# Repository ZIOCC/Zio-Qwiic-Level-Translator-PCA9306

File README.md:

# Zio Qwiic Level Translator (PCA9306)

> This product can be available for purchase [here](https://www.smart-prototyping.com/Zio-Qwiic-Level-Translator-PCA9306).

#### Description

Does your project use components with different voltages? There must be a way to match the output level of one device with the input voltage level of another device.To allow a proper translation of I2C signals from one voltage reference to another, both the high-level and low-level voltage thresholds need to be translated. No worries, we got you covered with the ZIO Qwiic Level Translator allowing bidirectional voltage translation from 1V to 3.6V and 1.8V to 5.5V on the high side.  

The board features a PCA9306 Dual bidirectional I2C bus and SMBUS voltage level translator without the use of a direction pin. Not only capable to match voltages but also frequencies, so it can be used to run two buses at different frequencies. One at 400 kHz operating frequency, and the other at 100 kHz.

As part of our Qwiic family, the setup is basic, just connect the lower voltage part to the connector next to SCL1, SDA1 and AREF1. The higher voltage part is connected the opposite connector next to SCL2, SDA2 and ARED2. 

We’ve also included the pinout in case you want to have the access directly to the connections. 

#### Specification

* Interface: I2C
* Allows voltage level translation between:
  * 1.0 V Vref(1) and 1.8 V, 2.5 V, 3.3 V or 5 V Vbias(ref)(2)
  * 1.2 V Vref(1) and 1.8 V, 2.5 V, 3.3 V or 5 V Vbias(ref)(2)
  * 1.8 V Vref(1) and 3.3 V or 5 V Vbias(ref)(2)
  * 2.5 V Vref(1) and 5 V Vbias(ref)(2)
  * 3.3 V Vref(1) and 5 V Vbias(ref)(2)
* Provides bidirectional voltage translation with no direction pin
* Less than 1.5 ns maximum propagation delay to accommodate Standard-mode and Fast-mode I2C-bus devices and multiple masters
* Low 3.5  ON-state connection between input and output ports provides less signal distortion
* Dimensions: 18.4 x 19.9mm
* Weight: 1.2g

#### Links

* [Eagle File and Schematic](https://github.com/ZIOCC/Zio-Qwiic-Level-Translator-PCA9306)
* [PCA9306 Datasheet](http://www.ti.com/lit/ds/symlink/pca9306.pdf)

> ###### About Zio
> Zio is a new line of open sourced, compact, and grid layout boards, fully integrated for Arduino and Qwiic ecosystem. Designed ideally for wearables, robotics, small-space limitations or other on the go projects. Check out other awesome Zio products [here](https://www.smart-prototyping.com/Zio).

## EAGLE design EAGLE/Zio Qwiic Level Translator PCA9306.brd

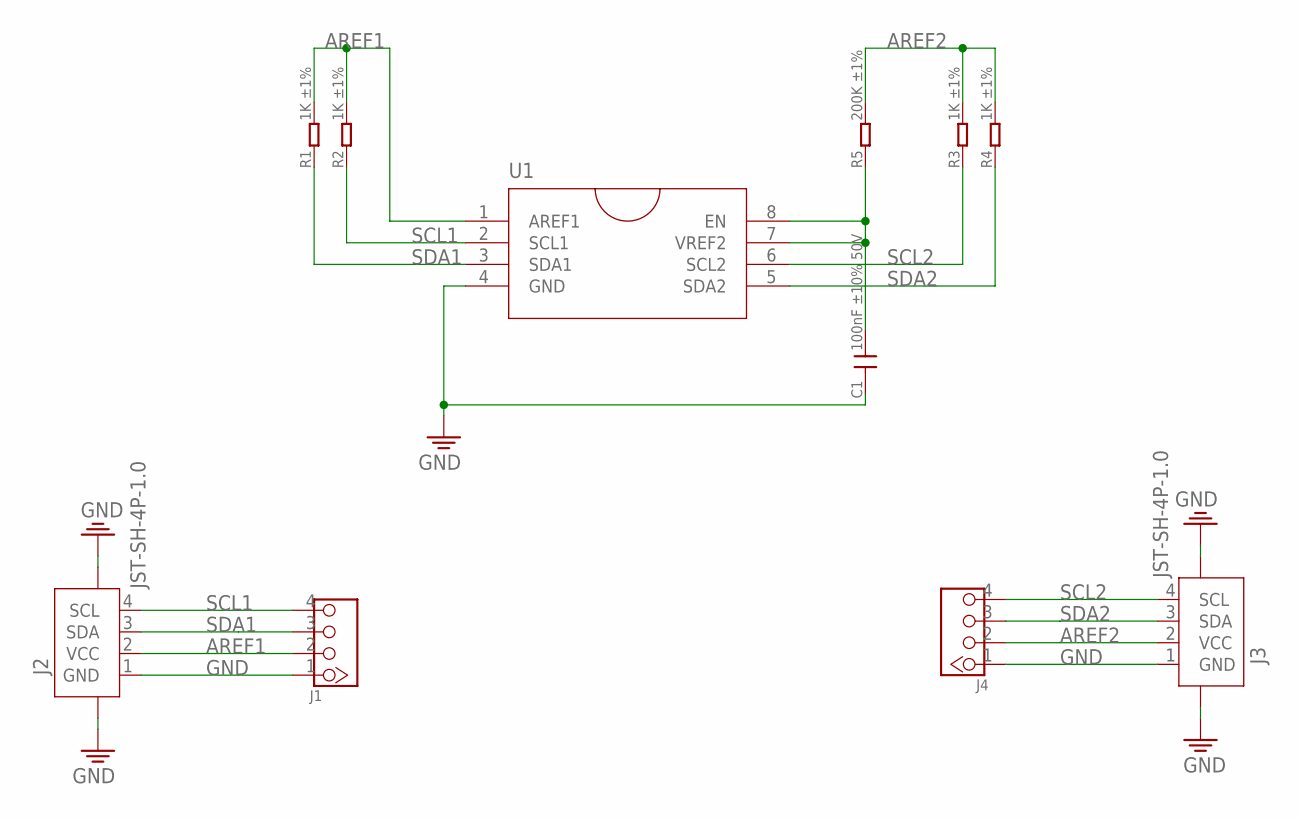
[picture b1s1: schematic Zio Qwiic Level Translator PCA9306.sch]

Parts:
C1: 100nF ±10% 50V; C0603
J1, J4: HEADER-4P-60/35MIL; 4P-65/35MIL
J2, J3: JST-SH-4P-1.0; JST-SH-4P
R1, R2, R3, R4: 1K ±1%; R0603
R5: 200K ±1%; R0603
U1: PCA9306DC; VSSOP-8

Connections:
AREF1: J1.2, J2.2 (VCC), R1.2, R2.2, U1.1 (AREF1)
AREF2: J3.2 (VCC), J4.2, R3.2, R4.2, R5.2
GND: C1.1, J1.1, J2.1 (GND), J2.NC1 (5), J2.NC2 (6), J3.1 (GND), J3.NC1 (5), J3.NC2 (6), J4.1, U1.4 (GND)
unnamed: C1.2, R5.1, U1.7 (VREF2), U1.8 (EN)
SCL1: J1.4, J2.4 (SCL), R2.1, U1.2 (SCL1)
SCL2: J3.4 (SCL), J4.4, R3.1, U1.6 (SCL2)
SDA1: J1.3, J2.3 (SDA), R1.1, U1.3 (SDA1)
SDA2: J3.3 (SDA), J4.3, R4.1, U1.5 (SDA2)

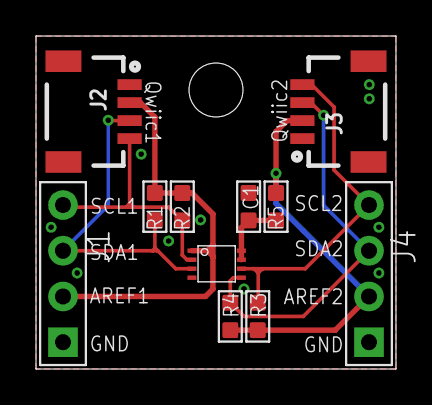
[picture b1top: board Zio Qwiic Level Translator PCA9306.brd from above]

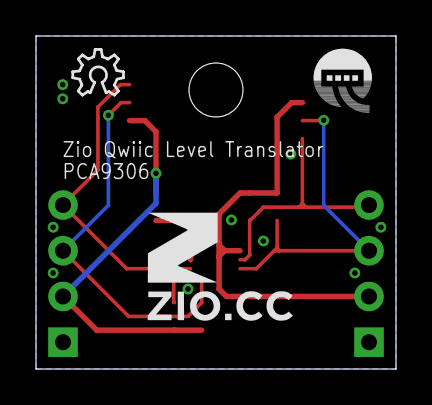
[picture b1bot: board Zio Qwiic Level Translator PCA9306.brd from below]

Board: 2 copper layers, 20.0 x 18.5 mm, 14 parts (3 on the bottom side), 8 nets.

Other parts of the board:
U$1: 6MM
U$2: OSHW_6X100_NOTEXT
U$3: QWIIC-LOGO-BASIC
